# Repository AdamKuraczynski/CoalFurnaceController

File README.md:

# CoalFurnaceController

This project utilizes an Arduino UNO R3 microcontroller as its base to control the pump and blower of a coal furnace. The repository includes all essential files and documents, detailing every step necessary for you to build it yourself.

#### Repository structure:
\PPT - This directory contains the presentation of the project in its initial, intermediate, and final stages. 

\SCH - This directory contains the complete project in Fusion 360 (along with its backup files) with all necessary libraries. It also contains PNG files with schematic and PCB layers.  

\SRC - This directory contains the source code, along with the necessary libraries required for compilation.  

\DOC\SPR - The directory contains all necessary documentation files for the project.  

## Other notes:

##### Hardware:  
Arduino UNO R3  
Breadboard 30  
USB B Cable  
Self-adhesive membrane keyboard 4x4 - 16 keys  
Temperature sensor DS18B20  
Diodes x 2  
Resistors 2x 330 Ohms, 1x 4.7 kOhms  
Pin Expander - Pcf8574 - I2C bus  
84x48 Nokia 5110 3310 display (pcd8544)  

##### Theory:
https://www.elektroda.pl/rtvforum/topic3668747.html   
https://forbot.pl/blog/kurs-elektroniki-prawa-ohma-i-kirchhoffa-id3986  

##### Schematic notes:
Project scanner I2C - checking ports ADDRESS 0x20  
(5-1.7) / 0.01 = 330 Ohms i.e., circuit power - V diode / diode operating range 0.005 to 0.02 = resistor value

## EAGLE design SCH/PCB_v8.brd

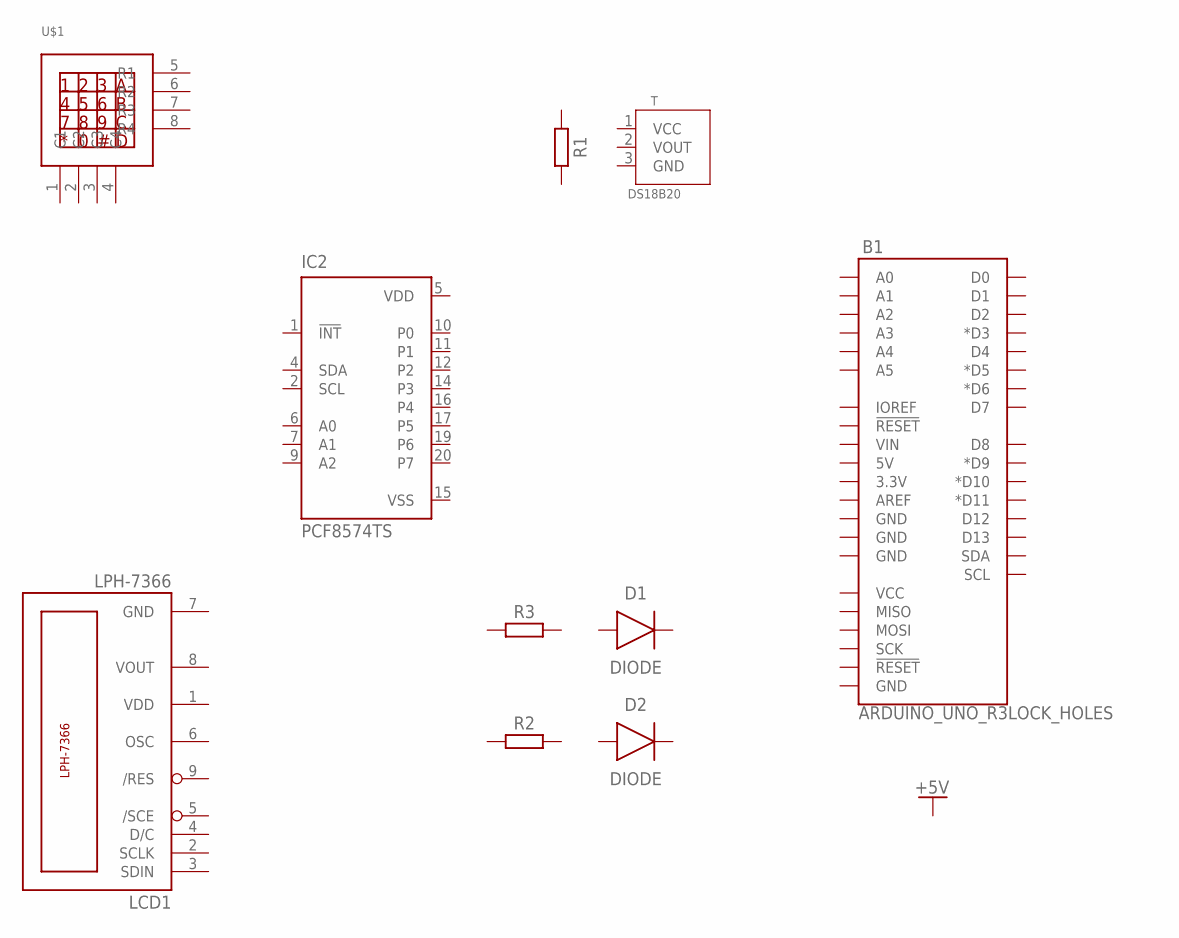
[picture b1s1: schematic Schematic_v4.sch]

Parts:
B1: ARDUINO_UNO_R3LOCK_HOLES; ARDUINO_R3_LOCK_HOLES
D1, D2: DIODE; DIOM7959X625N
IC2: PCF8574TS; SSOP20
LCD1: LPH-7366
R1, R2, R3: R_AXIAL-7.2MM-PITCH; RESAD724W46L381D178B
T: DS18B20; SOT95P285X113-3N; MPN DS18B20
U$1: KEYPAD4X4

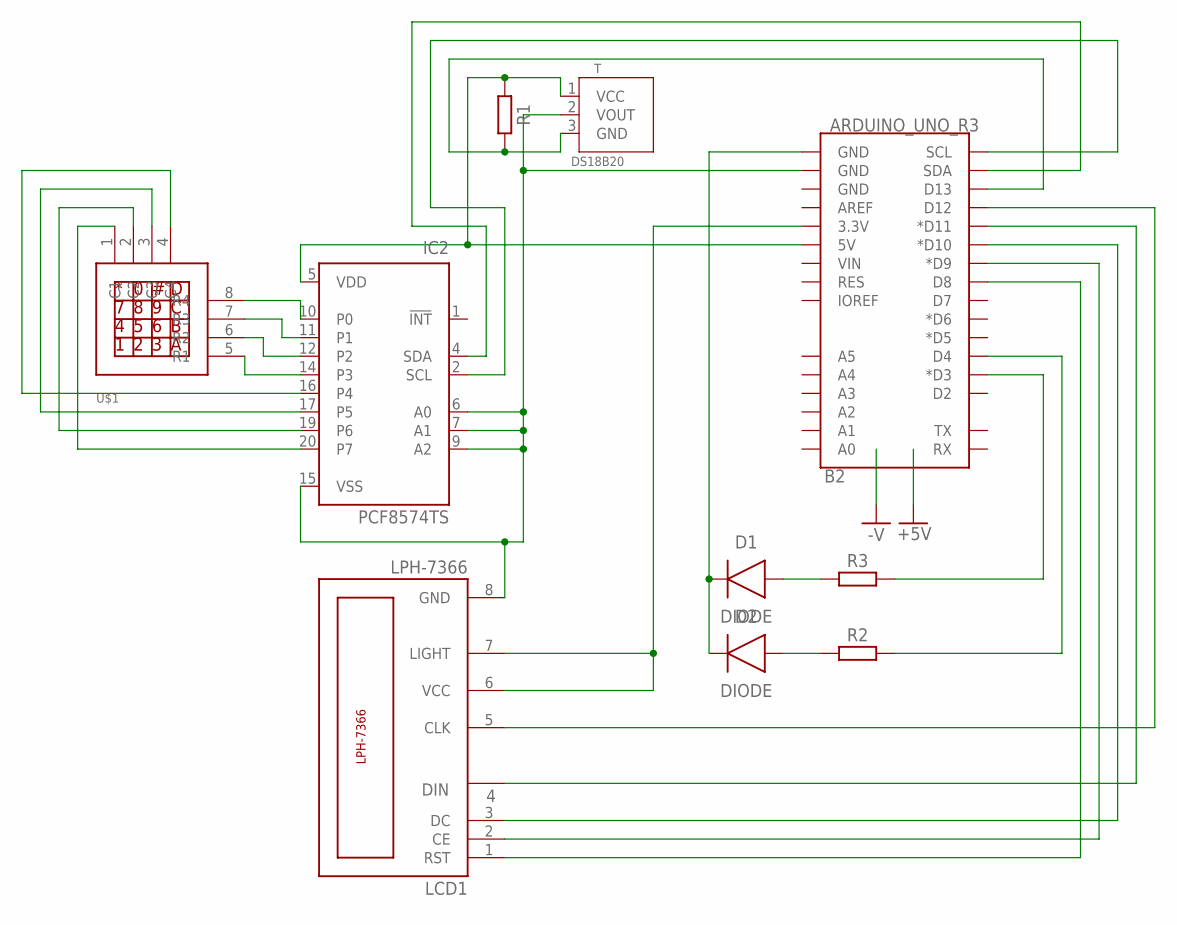
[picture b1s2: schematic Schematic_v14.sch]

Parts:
B2: ARDUINO_UNO_R3; UNO_R3_SHIELD_NOLABELS_LOCK
D1, D2: DIODE; DIOM7959X625N
IC2: PCF8574TS; SSOP20
LCD1: LPH-7366
R1, R2, R3: R_AXIAL-7.2MM-PITCH; RESAD724W46L381D178B
T: DS18B20; SOT95P285X113-3N; MPN DS18B20
U$1: KEYPAD4X4

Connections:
unnamed: B2.5V, IC2.5 (VDD), R1.1, T.1 (VCC)
unnamed: B2.D13, R1.2, T.3 (GND)
unnamed: D1.2 (A), R3.1
unnamed: B2.D3 (*D3), R3.2
unnamed: B2.D4, R2.2
unnamed: D2.2 (A), R2.1
unnamed: B2.GND@0 (GND), D1.1 (C), D2.1 (C)
unnamed: IC2.10 (P0), U$1.8 (R4)
unnamed: B2.GND@1 (GND), IC2.6 (A0), IC2.7 (A1), IC2.9 (A2), IC2.15 (VSS), LCD1.8 (GND), T.2 (VOUT)
unnamed: B2.SCL, IC2.2 (SCL)
unnamed: IC2.11 (P1), U$1.7 (R3)
unnamed: IC2.12 (P2), U$1.6 (R2)
unnamed: IC2.14 (P3), U$1.5 (R1)
unnamed: IC2.20 (P7), U$1.1 (C1)
unnamed: IC2.19 (P6), U$1.2 (C2)
unnamed: IC2.17 (P5), U$1.3 (C3)
unnamed: IC2.16 (P4), U$1.4 (C4)
unnamed: B2.SDA, IC2.4 (SDA)
unnamed: B2.D8, LCD1.1 (RST)
unnamed: B2.D9 (*D9), LCD1.2 (CE)
unnamed: B2.D10 (*D10), LCD1.3 (DC)
unnamed: B2.D11 (*D11), LCD1.4 (DIN)
unnamed: B2.D12, LCD1.5 (CLK)
unnamed: B2.3.3V, LCD1.6 (VCC), LCD1.7 (LIGHT)

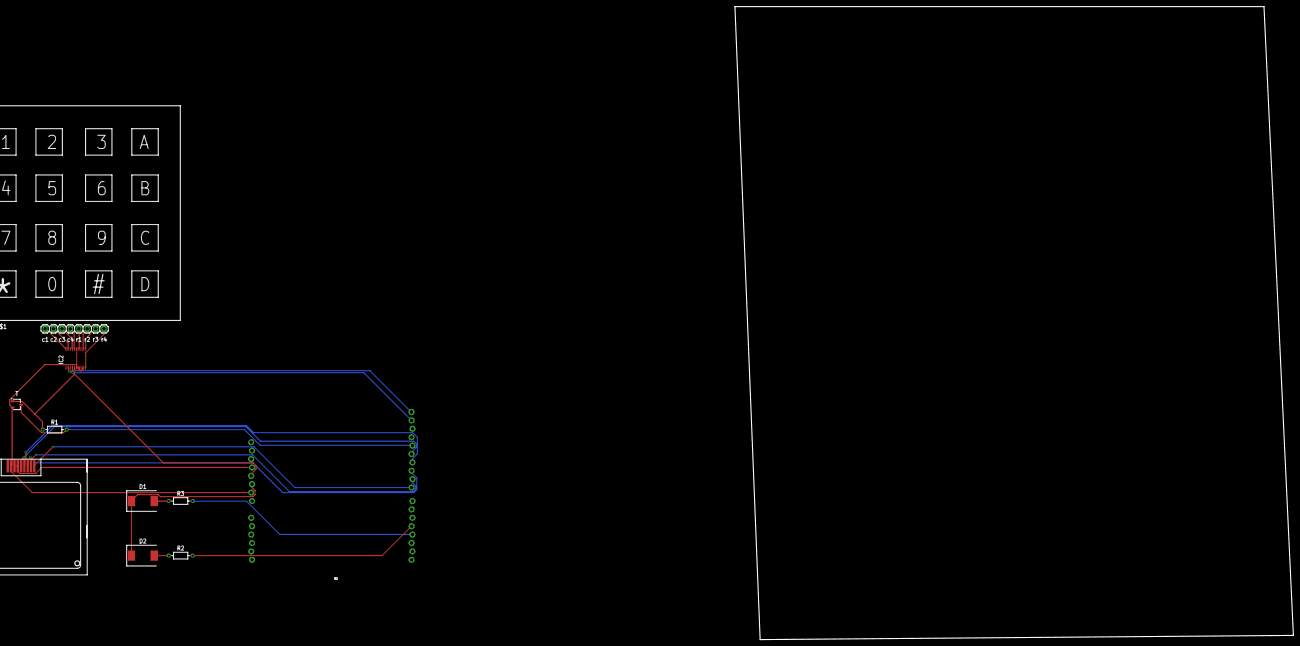
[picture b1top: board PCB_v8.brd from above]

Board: 2 copper layers, 168.9 x 191.4 mm, 10 parts (0 on the bottom side), 24 nets.

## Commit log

2024-02-18 Version 1.0
2024-02-18 Delete ReadMe.txt
    Delete due to duplicate
2024-02-20 Full documentation

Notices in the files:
parts and their libraries:
SparkFun-Boards: Licensing: Creative Commons ShareAlike 4.0 International - https://creativecommons.org/licenses/by-sa/4.0
